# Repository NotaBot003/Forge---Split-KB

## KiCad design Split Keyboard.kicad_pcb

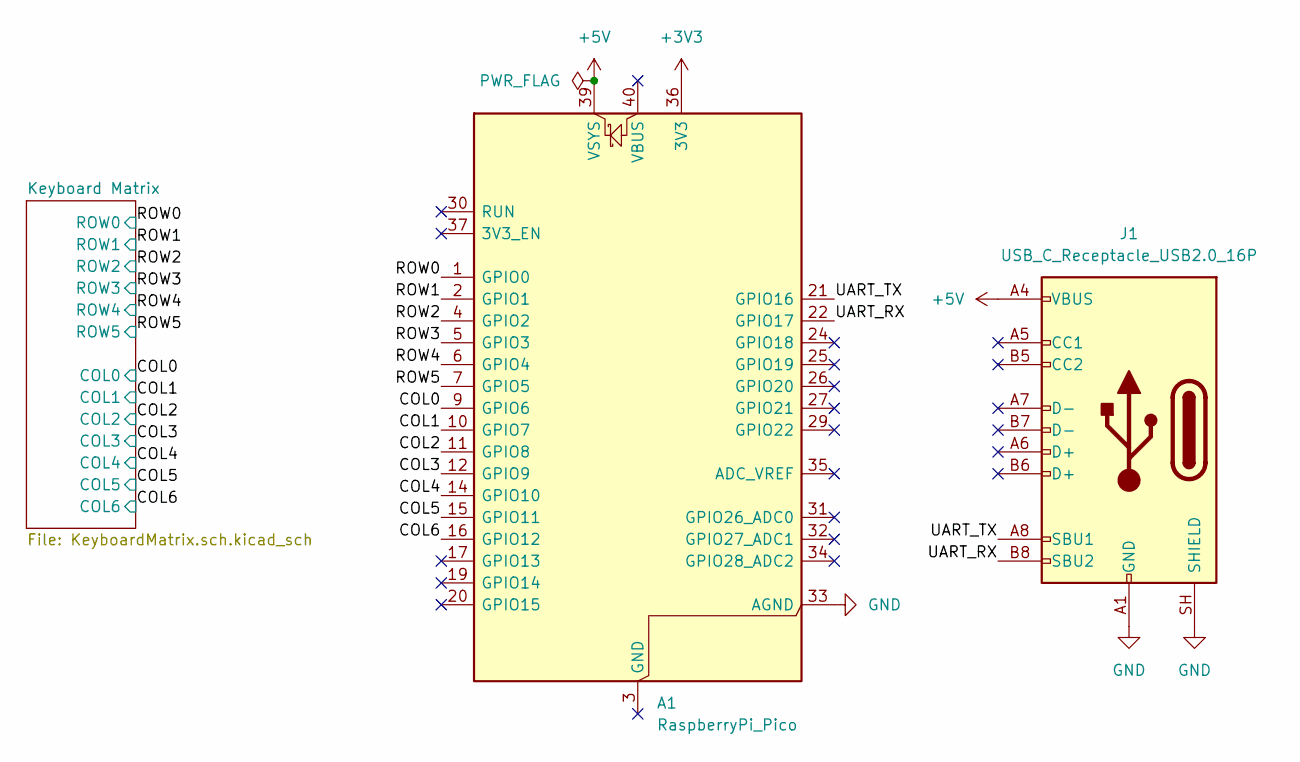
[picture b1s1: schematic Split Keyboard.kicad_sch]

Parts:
A1: RaspberryPi_Pico; RaspberryPi_Pico_Common_Unspecified
J1: USB_C_Receptacle_USB2.0_16P; USB_C_Receptacle_XKB_U262-16XN-4BVC11

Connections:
+3V3: A1.36 (3V3)
+5V: A1.39 (VSYS), J1.A4 (VBUS), J1.A9 (VBUS), J1.B4 (VBUS), J1.B9 (VBUS)
/COL0: A1.9 (GPIO6); also elsewhere on the board
/COL1: A1.10 (GPIO7); also elsewhere on the board
/COL2: A1.11 (GPIO8); also elsewhere on the board
/COL3: A1.12 (GPIO9); also elsewhere on the board
/COL4: A1.14 (GPIO10); also elsewhere on the board
/COL5: A1.15 (GPIO11); also elsewhere on the board
/COL6: A1.16 (GPIO12); also elsewhere on the board
/ROW0: A1.1 (GPIO0); also elsewhere on the board
/ROW1: A1.2 (GPIO1); also elsewhere on the board
/ROW2: A1.4 (GPIO2); also elsewhere on the board
/ROW3: A1.5 (GPIO3); also elsewhere on the board
/ROW4: A1.6 (GPIO4); also elsewhere on the board
/ROW5: A1.7 (GPIO5); also elsewhere on the board
/UART_RX: A1.22 (GPIO17), J1.B8 (SBU2)
/UART_TX: A1.21 (GPIO16), J1.A8 (SBU1)
GND: A1.33 (AGND), J1.A1 (GND), J1.A12 (GND), J1.B1 (GND), J1.B12 (GND), J1.SH (SHIELD)

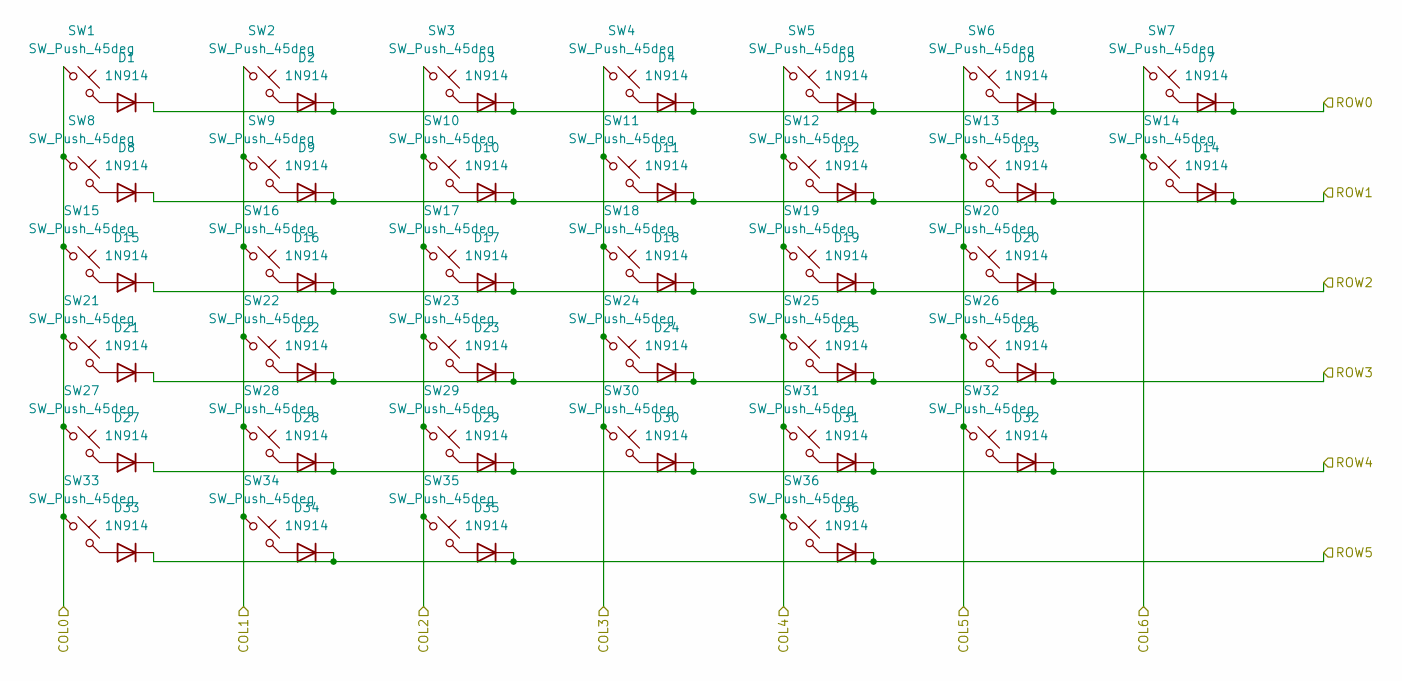
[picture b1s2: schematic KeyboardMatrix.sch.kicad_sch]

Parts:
D1, D2, D3, D4, D5, D6, D7, D8, D9, D10, D11, D12, D13, D14, D15, D16, D17, D18, D19, D20, D21, D22, D23, D24, D25, D26, D27, D28, D29, D30, D31, D32, D33, D34, D35, D36: 1N914; D_DO-35_SOD27_P7.62mm_Horizontal
SW1, SW2, SW3, SW4, SW5, SW6, SW7, SW8, SW9, SW10, SW11, SW12, SW13, SW14, SW15, SW16, SW17, SW18, SW19, SW20, SW21, SW22, SW23, SW24, SW25, SW26, SW27, SW28, SW29, SW30, SW31, SW32, SW33, SW34, SW35, SW36: SW_Push_45deg; MX_PCB_1.00u

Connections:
/COL0: SW1.1, SW8.1, SW15.1, SW21.1, SW27.1, SW33.1; also elsewhere on the board
/COL1: SW2.1, SW9.1, SW16.1, SW22.1, SW28.1, SW34.1; also elsewhere on the board
/COL2: SW3.1, SW10.1, SW17.1, SW23.1, SW29.1, SW35.1; also elsewhere on the board
/COL3: SW4.1, SW11.1, SW18.1, SW24.1, SW30.1; also elsewhere on the board
/COL4: SW5.1, SW12.1, SW19.1, SW25.1, SW31.1, SW36.1; also elsewhere on the board
/COL5: SW6.1, SW13.1, SW20.1, SW26.1, SW32.1; also elsewhere on the board
/COL6: SW7.1, SW14.1; also elsewhere on the board
/ROW0: D1.1 (K), D2.1 (K), D3.1 (K), D4.1 (K), D5.1 (K), D6.1 (K), D7.1 (K); also elsewhere on the board
/ROW1: D8.1 (K), D9.1 (K), D10.1 (K), D11.1 (K), D12.1 (K), D13.1 (K), D14.1 (K); also elsewhere on the board
/ROW2: D15.1 (K), D16.1 (K), D17.1 (K), D18.1 (K), D19.1 (K), D20.1 (K); also elsewhere on the board
/ROW3: D21.1 (K), D22.1 (K), D23.1 (K), D24.1 (K), D25.1 (K), D26.1 (K); also elsewhere on the board
/ROW4: D27.1 (K), D28.1 (K), D29.1 (K), D30.1 (K), D31.1 (K), D32.1 (K); also elsewhere on the board
/ROW5: D33.1 (K), D34.1 (K), D35.1 (K), D36.1 (K); also elsewhere on the board
unnamed: D1.2 (A), SW1.2
unnamed: D2.2 (A), SW2.2
unnamed: D3.2 (A), SW3.2
unnamed: D4.2 (A), SW4.2
unnamed: D5.2 (A), SW5.2
unnamed: D6.2 (A), SW6.2
unnamed: D7.2 (A), SW7.2
unnamed: D8.2 (A), SW8.2
unnamed: D9.2 (A), SW9.2
unnamed: D10.2 (A), SW10.2
unnamed: D11.2 (A), SW11.2
unnamed: D12.2 (A), SW12.2
unnamed: D13.2 (A), SW13.2
unnamed: D14.2 (A), SW14.2
unnamed: D15.2 (A), SW15.2
unnamed: D16.2 (A), SW16.2
unnamed: D17.2 (A), SW17.2
unnamed: D18.2 (A), SW18.2
unnamed: D19.2 (A), SW19.2
unnamed: D20.2 (A), SW20.2
unnamed: D21.2 (A), SW21.2
unnamed: D22.2 (A), SW22.2
unnamed: D23.2 (A), SW23.2
unnamed: D24.2 (A), SW24.2
unnamed: D25.2 (A), SW25.2
unnamed: D26.2 (A), SW26.2
unnamed: D27.2 (A), SW27.2
unnamed: D28.2 (A), SW28.2
unnamed: D29.2 (A), SW29.2
unnamed: D30.2 (A), SW30.2
unnamed: D31.2 (A), SW31.2
unnamed: D32.2 (A), SW32.2
unnamed: D33.2 (A), SW33.2
unnamed: D34.2 (A), SW34.2
unnamed: D35.2 (A), SW35.2
unnamed: D36.2 (A), SW36.2

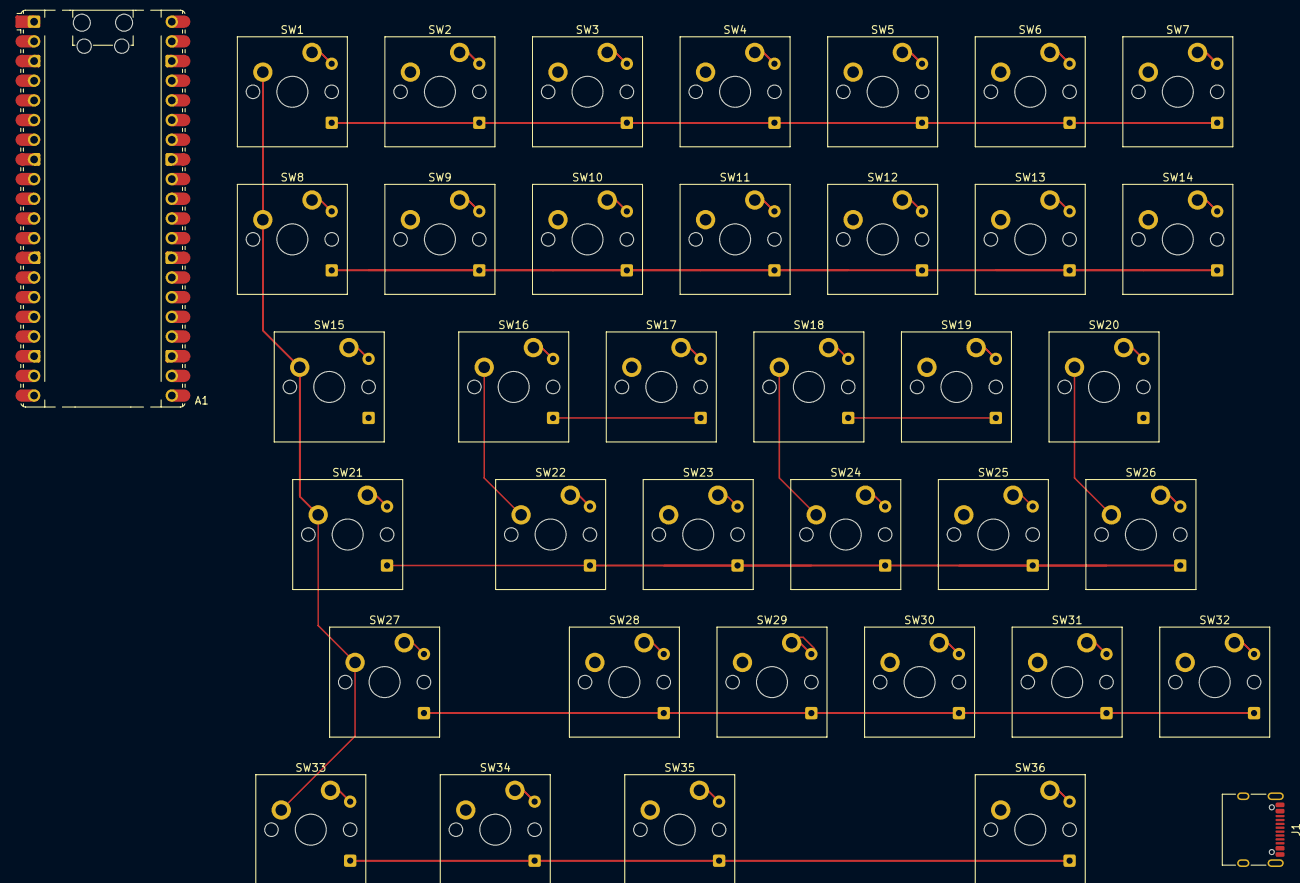
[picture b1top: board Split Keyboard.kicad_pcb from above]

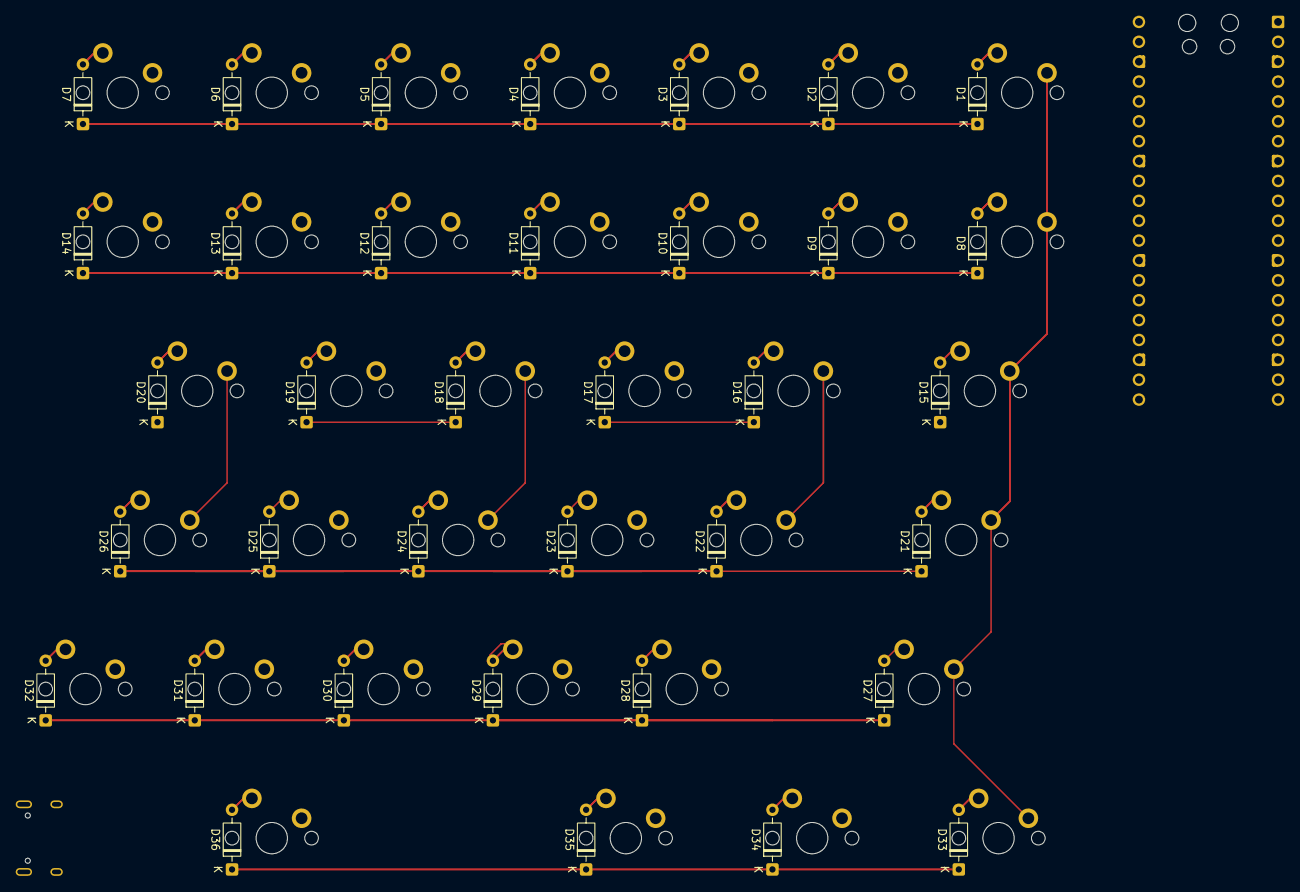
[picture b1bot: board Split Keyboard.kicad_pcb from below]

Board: 2 copper layers, 74 parts (36 on the bottom side), 53 nets.

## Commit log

2026-06-11 Initial commit
    All the progress I made so far
2026-06-11 Created the PCB layout
